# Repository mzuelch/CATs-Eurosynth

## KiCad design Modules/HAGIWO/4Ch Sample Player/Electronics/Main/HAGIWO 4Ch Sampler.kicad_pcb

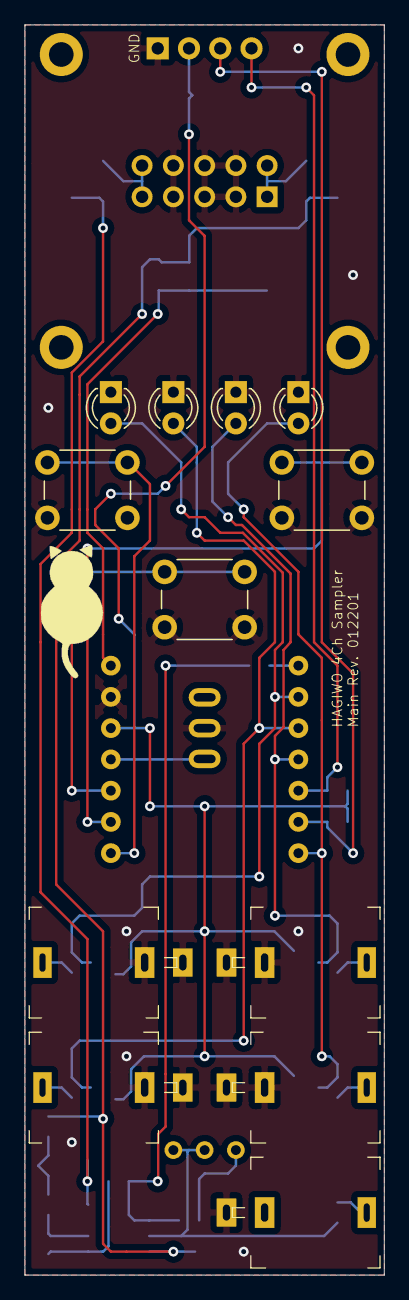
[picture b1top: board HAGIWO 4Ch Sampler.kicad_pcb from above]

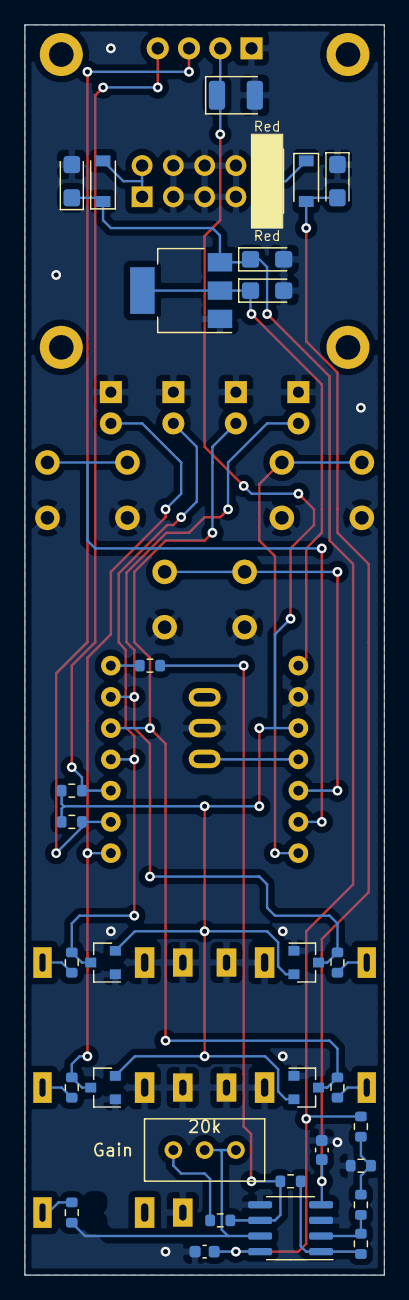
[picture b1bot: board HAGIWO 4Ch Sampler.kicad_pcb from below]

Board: 2 copper layers, 29.2 x 101.6 mm, 46 parts (32 on the bottom side), 29 nets.

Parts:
C1: 100uF/6.3V; CP_EIA-3528-21_Kemet-B
C3, C4, C5, C7: 10uF/16V; CP_EIA-3216-18_Kemet-A
C6, C8: 100n; C_0603_1608Metric
D1, D2, D5, D6: BAV99; SOT-23
D3: Ch 1; LED_D3.0mm
D4: Ch 3; LED_D3.0mm
D7: Ch 2; LED_D3.0mm
D8: Ch 4; LED_D3.0mm
D9, D10: B5819W SL; D_SOD-123
DISP1: MC096xx; 0.96inch_OLED_MC096GX
J1: Ch. 1 In; Jack_3.5mm_QingPu_WQP-PJ301M-12
J2: Ch. 3 In; Jack_3.5mm_QingPu_WQP-PJ301M-12
J3: Ch. 2 In; Jack_3.5mm_QingPu_WQP-PJ301M-12
J4: Ch. 4 In; Jack_3.5mm_QingPu_WQP-PJ301M-12
J5: Out; Jack_3.5mm_QingPu_WQP-PJ301M-12
J6: Power; Power_2x5_Vertical
R1, R2: 3k3; R_0603_1608Metric
R3, R4, R7, R8: 33k; R_0603_1608Metric
R5: 7k5; R_0603_1608Metric
R6, R9, R10, R13: 10k; R_0603_1608Metric
R11: 27k; R_0603_1608Metric
R12: 1k5; R_0603_1608Metric
R14: 1k; R_0603_1608Metric
SW1: Left; SW_PUSH_6mm
SW2: Right; SW_PUSH_6mm
SW3: Down; SW_PUSH_6mm
SW4: Mode; SMTS-1xx-Solder
T1: 20k; Potentiometer_Bourns_3296W_Vertical
U1: TL072CDT; SOIC-8_3.9x4.9mm_P1.27mm
U2: SeeeduinoXIAOPin; Seeeduino XIAO Pin
U3: AMS1117-5.0; SOT-223-3_TabPin2

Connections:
+3V3: C1.1, D1.2, D2.2, D5.2, D6.2, DISP1.VCC, R1.2, R2.2, U2.12
+5V: C5.1, U2.14, U3.2
+12V: C3.1, C4.1, C6.2, D9.1, R5.2, U1.8, U3.3
-12V: C7.2, C8.1, D10.2, U1.4
A7: SW1.1, U2.8
A8: SW2.1, U2.9
A9: SW3.1, U2.10
D1: D1.3, D3.2, R3.1, U2.2
D2: D5.3, D7.2, R7.1, U2.3
D3: D2.3, D4.2, R4.1, U2.4
D4: D6.3, D8.2, R8.1, U2.7
D10: SW4.2, U2.11
DAC: R13.2, U2.1
GND: C1.2, C3.2, C4.2, C5.2, C6.1, C7.1, C8.2, D1.1, D2.1, D3.1, D4.1, D5.1, D6.1, D7.1, D8.1, DISP1.GND, J1.S, J1.TN, J2.S, J2.TN, J3.S, J3.TN, J4.S, J4.TN, J5.S, J6.GND, R12.1, SW1.2, SW2.2, SW3.2, SW4.1, U1.3, U1.5, U2.13, U3.1
unnamed: D9.2, J6.+12V
unnamed: D10.1, J6.-12V
unnamed: J1.T, R3.2
unnamed: J2.T, R4.2
unnamed: J3.T, R7.2
unnamed: J4.T, R8.2
unnamed: J5.T, R14.1
unnamed: R6.2, R9.1, U1.2
unnamed: R10.1, R11.2, R13.1, U1.6
unnamed: R6.1, R10.2, U1.1
unnamed: R11.1, T1.1
unnamed: R5.1, R9.2, R12.2
unnamed: R14.2, T1.2, T1.3, U1.7
SCL: DISP1.SCL, R2.1, U2.6
SDA: DISP1.SDA, R1.1, U2.5

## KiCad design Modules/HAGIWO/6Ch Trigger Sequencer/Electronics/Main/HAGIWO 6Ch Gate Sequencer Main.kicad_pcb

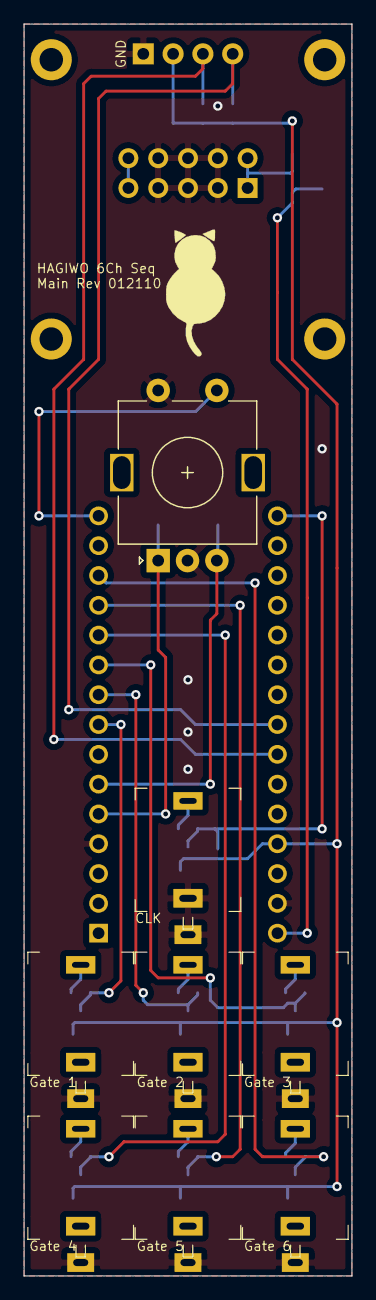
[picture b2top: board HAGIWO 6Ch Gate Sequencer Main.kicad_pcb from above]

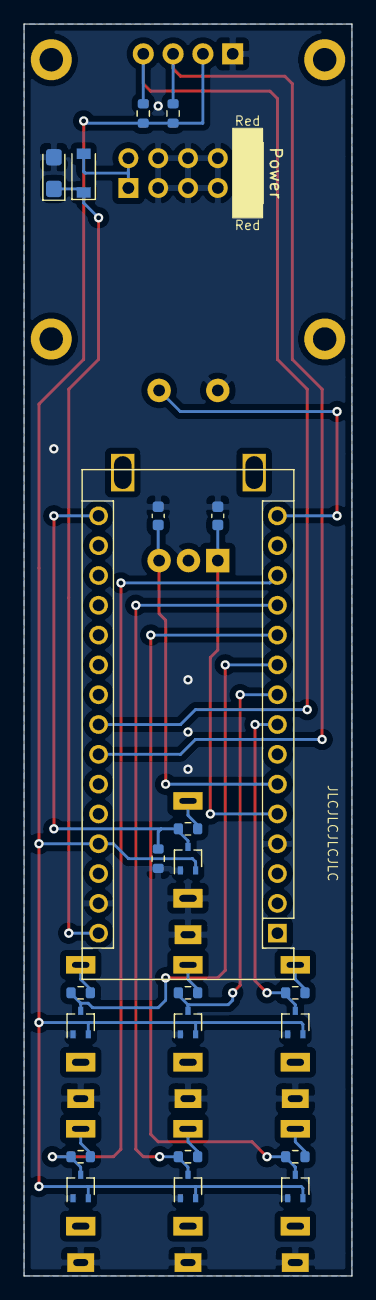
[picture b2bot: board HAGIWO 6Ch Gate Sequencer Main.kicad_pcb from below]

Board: 2 copper layers, 27.9 x 106.7 mm, 32 parts (23 on the bottom side), 23 nets.

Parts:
A1: Arduino_Nano_v3.x; Arduino_Nano
C1: 10µF/16V; CP_EIA-3216-18_Kemet-A
C7, C8: 10n; C_0603_1608Metric
D1: B5817W; D_SOD-123
D2, D3, D4, D5, D6, D7, D8: BAV99W; SOT-323_SC-70
DISP1: MC096xx; MC096Gx
J1: Power; Power_2x5_Vertical
J2: Gate 2; Jack_3.5mm_QingPu_WQP-PJ301M-12
J3: CLK; Jack_3.5mm_QingPu_WQP-PJ301M-12
J4: Gate 1; Jack_3.5mm_QingPu_WQP-PJ301M-12
J5: Gate 3; Jack_3.5mm_QingPu_WQP-PJ301M-12
J6: Gate 4; Jack_3.5mm_QingPu_WQP-PJ301M-12
J7: Gate 5; Jack_3.5mm_QingPu_WQP-PJ301M-12
J8: Gate 6; Jack_3.5mm_QingPu_WQP-PJ301M-12
R1, R4, R5, R6, R8, R9, R10: 470R; R_0603_1608Metric
R2: 100k; R_0603_1608Metric
R3, R7: 3k3; R_0603_1608Metric
SW2: Encoder; RotaryEncoder_Alps_EC11E-Switch_Vertical_H20mm

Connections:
+5V: A1.27, D2.2, D3.2, D4.2, D5.2, D6.2, D7.2, D8.2, DISP1.VCC, R3.2, R7.2
+12V: A1.30, C1.1, D1.1
+12VA: D1.2, J1.+12V
CLK: A1.16, D2.3, R1.1, R2.2
ENC_A: A1.5, C7.1, SW2.A
ENC_B: A1.6, C8.1, SW2.B
ENC_SW: A1.15, SW2.S1
G1: A1.8, D3.3, R4.2
G2: A1.9, D4.3, R5.2
G3: A1.10, D5.3, R6.2
G4: A1.11, D6.3, R8.2
G5: A1.12, D7.3, R9.2
G6: A1.13, D8.3, R10.2
GND: A1.4, A1.29, C1.2, C7.2, C8.2, D2.1, D3.1, D4.1, D5.1, D6.1, D7.1, D8.1, DISP1.GND, J1.GND, J2.S, J3.S, J3.TN, J4.S, J5.S, J6.S, J7.S, J8.S, R2.1, SW2.C, SW2.S2
unnamed: J2.T, R5.1
unnamed: J3.T, R1.2
unnamed: J4.T, R4.1
unnamed: J5.T, R6.1
unnamed: J6.T, R8.1
unnamed: J7.T, R9.1
unnamed: J8.T, R10.1
SCL: A1.24, DISP1.SCL, R7.1
SDA: A1.23, DISP1.SDA, R3.1
